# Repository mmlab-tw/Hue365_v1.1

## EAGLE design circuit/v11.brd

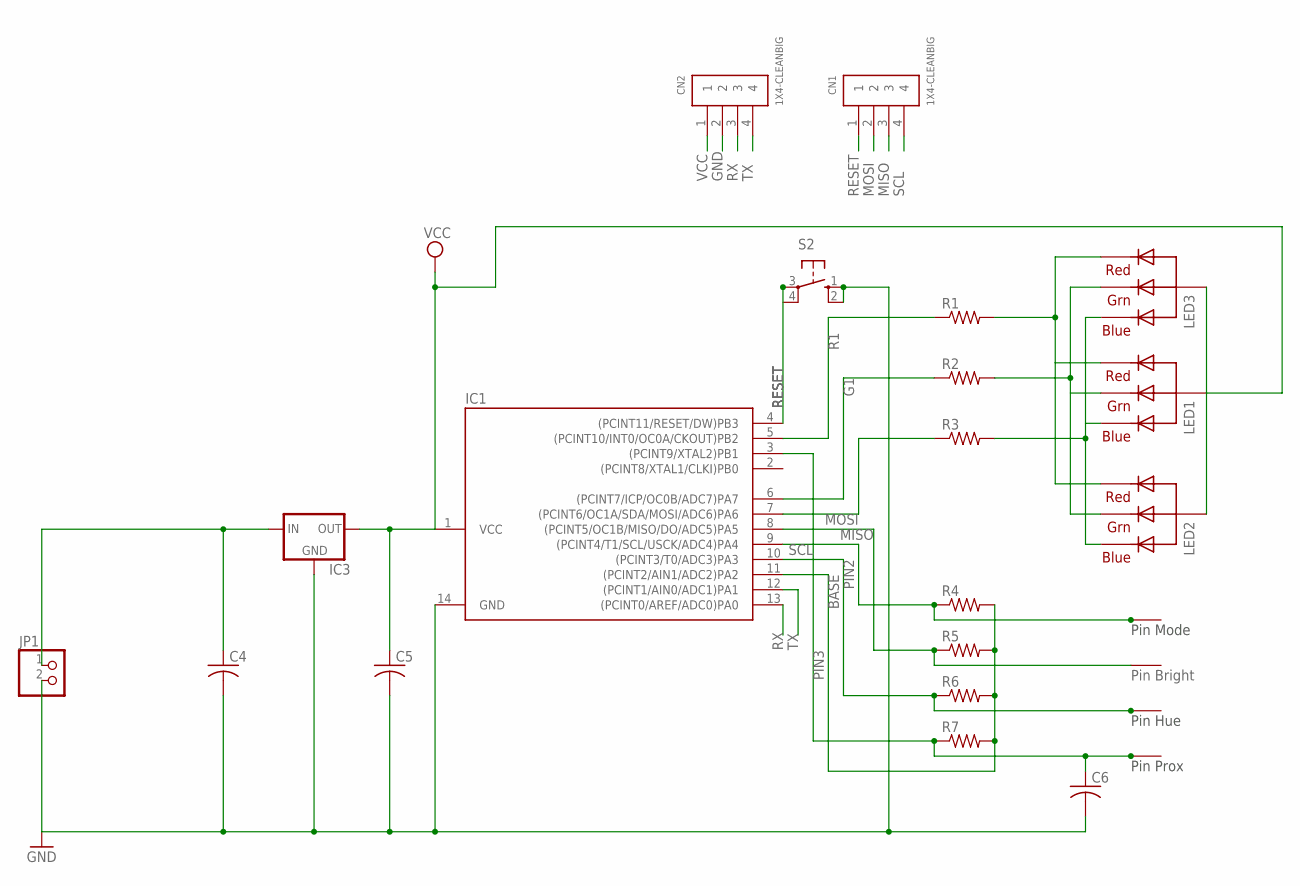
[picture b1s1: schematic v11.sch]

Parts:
2: TOUCH; RENG
C4, C5, C6: C-USC0603; C0603
CN1, CN2: 1X4-CLEANBIG; 1X04-CLEANBIG
IC1: TINY24/44/84-PU; DIL14
IC3: 78LXX
JP1: PINHD-1X2/90; 1X02/90
LED1, LED2, LED3: RGBLED_CA-5MM; LED5MMRGB
PIN_PROX: TOUCH; RENG
PROX_PIN: TOUCH; RENG
R1, R2, R3, R4, R5, R6, R7: R-US_R0603; R0603
S2: 10-XX; B3F-10XX
U$3: TOUCH; RENG

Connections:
B: LED1.4 (BLUE), LED2.4 (BLUE), LED3.4 (BLUE), R3.2
BASE: IC1.11 ((PCINT2/AIN1/ADC2)PA2), R4.2, R5.2, R6.2, R7.2
G: LED1.3 (GREEN), LED2.3 (GREEN), LED3.3 (GREEN), R2.2
G1: IC1.6 ((PCINT7/ICP/OC0B/ADC7)PA7), R2.1
GND: C4.2, C5.2, C6.2, CN2.2, IC1.14 (GND), IC3.GND, JP1.2, S2.1 (S), S2.2 (S1)
MISO: 2.T, CN1.3, IC1.8 ((PCINT5/OC1B/MISO/DO/ADC5)PA5), R5.1
MOSI: CN1.2, IC1.7 ((PCINT6/OC1A/SDA/MOSI/ADC6)PA6), R3.1
unnamed: C4.1, IC3.IN, JP1.1
PIN2: IC1.10 ((PCINT3/T0/ADC3)PA3), R6.1, U$3.T
PIN3: C6.1, IC1.3 ((PCINT9/XTAL2)PB1), PROX_PIN.T, R7.1
R: LED1.1 (RED), LED2.1 (RED), LED3.1 (RED), R1.2
R1: IC1.5 ((PCINT10/INT0/OC0A/CKOUT)PB2), R1.1
RESET: CN1.1, IC1.4 ((PCINT11/RESET/DW)PB3), S2.3
RX: CN2.3, IC1.13 ((PCINT0/AREF/ADC0)PA0)
SCL: CN1.4, IC1.9 ((PCINT4/T1/SCL/USCK/ADC4)PA4), PIN_PROX.T, R4.1
TX: CN2.4, IC1.12 ((PCINT1/AIN0/ADC1)PA1)
VCC: C5.1, CN2.1, IC1.1 (VCC), IC3.OUT, LED1.2 (VCC), LED2.2 (VCC), LED3.2 (VCC)

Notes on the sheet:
Pin Prox
Pin Hue
Pin Bright
Pin Mode

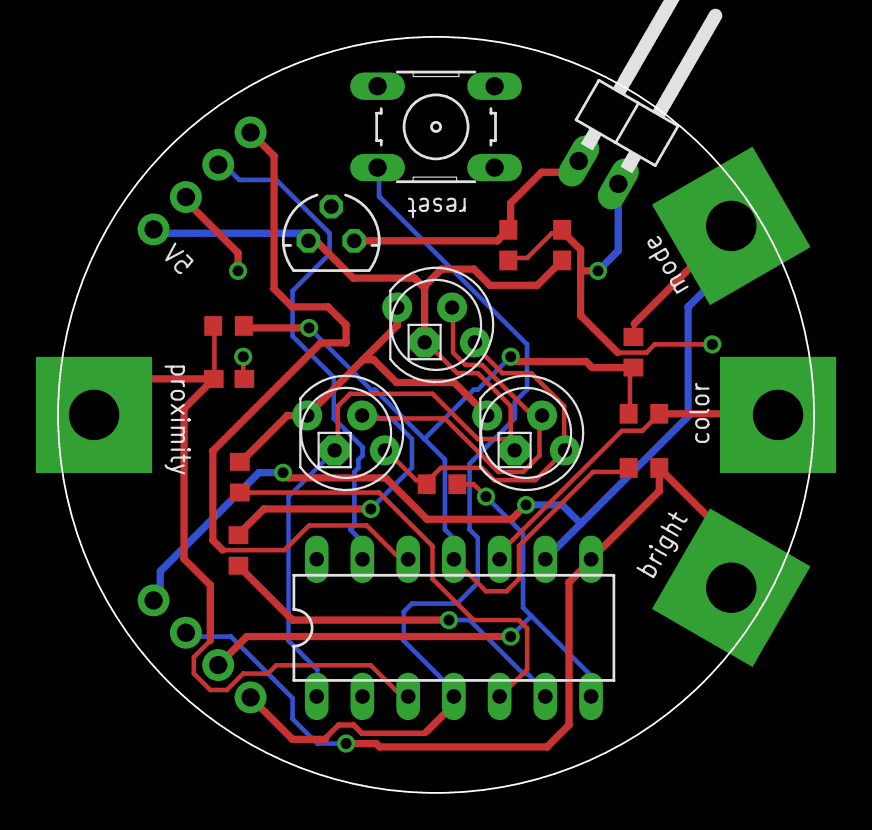
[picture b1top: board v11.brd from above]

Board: 2 copper layers, 42.0 x 42.0 mm, 23 parts (0 on the bottom side), 17 nets.

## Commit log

2018-12-25 Hue365 v1.1
    A smaller board, more reliable code, and a cubic model.
